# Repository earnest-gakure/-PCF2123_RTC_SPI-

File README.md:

# -PCF2123_RTC_SPI-
## Designed in KiCad
  The PCF2123 is a CMOS1 Real-Time Clock (RTC) and calendar optimized for low power applications. Data is transferred serially via a Serial Peripheral Interface (SPI-bus).

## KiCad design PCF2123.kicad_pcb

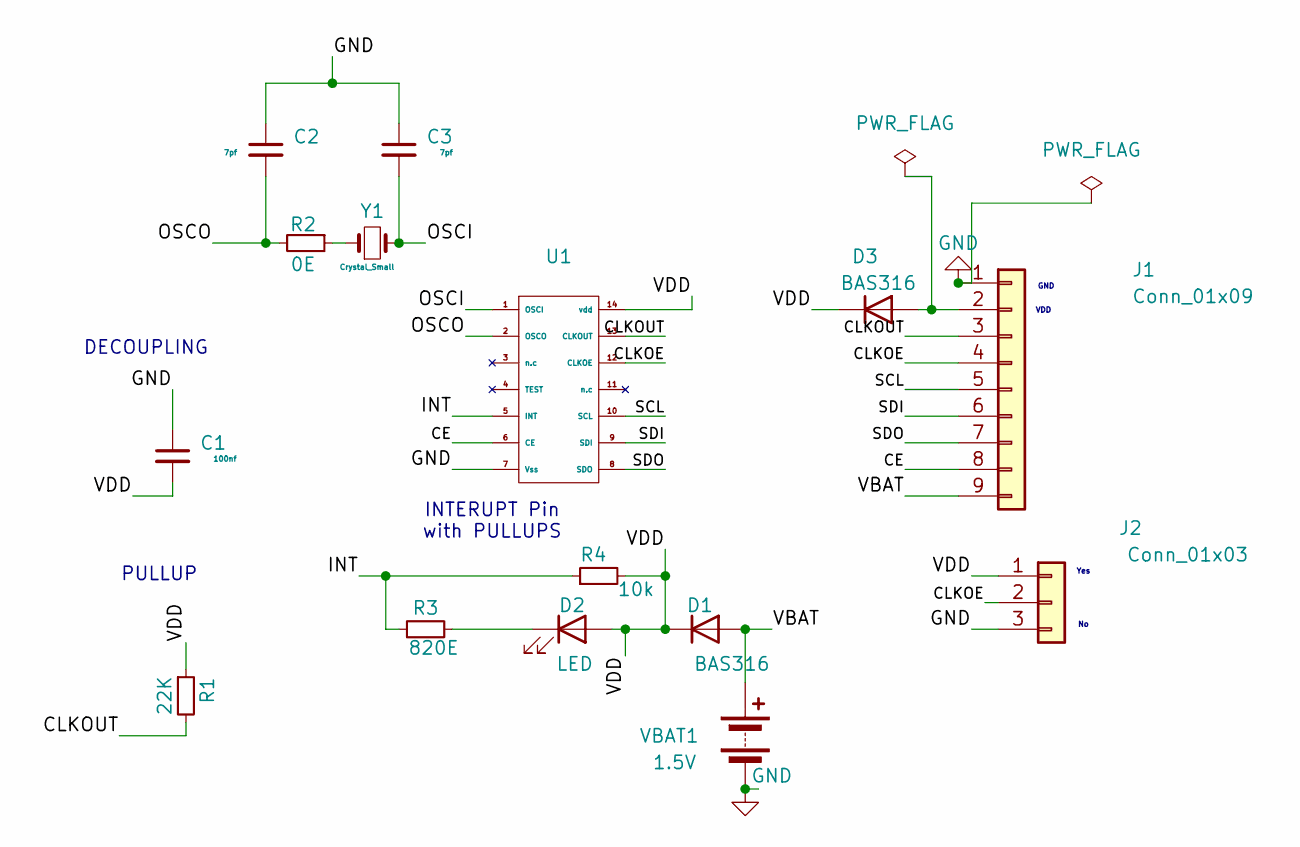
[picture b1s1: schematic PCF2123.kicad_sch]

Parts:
C1: 100nf; C_0805_2012Metric_Pad1.18x1.45mm_HandSolder
C2, C3: 7pf; C_0805_2012Metric_Pad1.18x1.45mm_HandSolder
D1, D3: BAS316; D_SMA-SMB_Universal_Handsoldering
D2: LED; LED_0805_2012Metric_Pad1.15x1.40mm_HandSolder
J1: Conn_01x09; PinHeader_1x09_P2.54mm_Vertical
J2: Conn_01x03; PinHeader_1x03_P2.54mm_Vertical
R1: 22K; R_1206_3216Metric_Pad1.30x1.75mm_HandSolder
R2: 0E; R_1206_3216Metric_Pad1.30x1.75mm_HandSolder
R3: 820E; R_1206_3216Metric_Pad1.30x1.75mm_HandSolder
R4: 10k; R_1206_3216Metric_Pad1.30x1.75mm_HandSolder
U1: PCF2123TS_RTC
VBAT1: 1.5V; BatteryHolder_ComfortableElectronic_CH273-2450_1x2450
Y1: Crystal_Small; Crystal_AT310_D3.0mm_L10.0mm_Horizontal

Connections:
/CE: J1.8, U1.6 (CE)
/CLKOE: J1.4, J2.2, U1.12 (CLKOE)
/CLKOUT: J1.3, R1.2, U1.13 (CLKOUT)
/INT: R3.1, R4.1, U1.5 (INT)
/OSCI: C3.2, U1.1 (OSCI), Y1.2
/OSCO: C2.2, R2.2, U1.2 (OSCO)
/SCL: J1.5, U1.10 (SCL)
/SDI: J1.6, U1.9 (SDI)
/SDO: J1.7, U1.8 (SDO)
/VBAT: D1.2 (A), J1.9, VBAT1.1 (+)
/VDD: C1.2, D1.1 (K), D2.2 (A), D3.1 (K), J2.1, R1.1, R4.2, U1.14 (vdd)
GND: C1.1, C2.1, C3.1, J1.1, J2.3, U1.7 (Vss), VBAT1.2 (-)
unnamed: D2.1 (K), R3.2
unnamed: D3.2 (A), J1.2
unnamed: R2.1, Y1.1

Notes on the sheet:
GND
PULLUP
INTERUPT Pin with PULLUPS
DECOUPLING
VDD
Yes

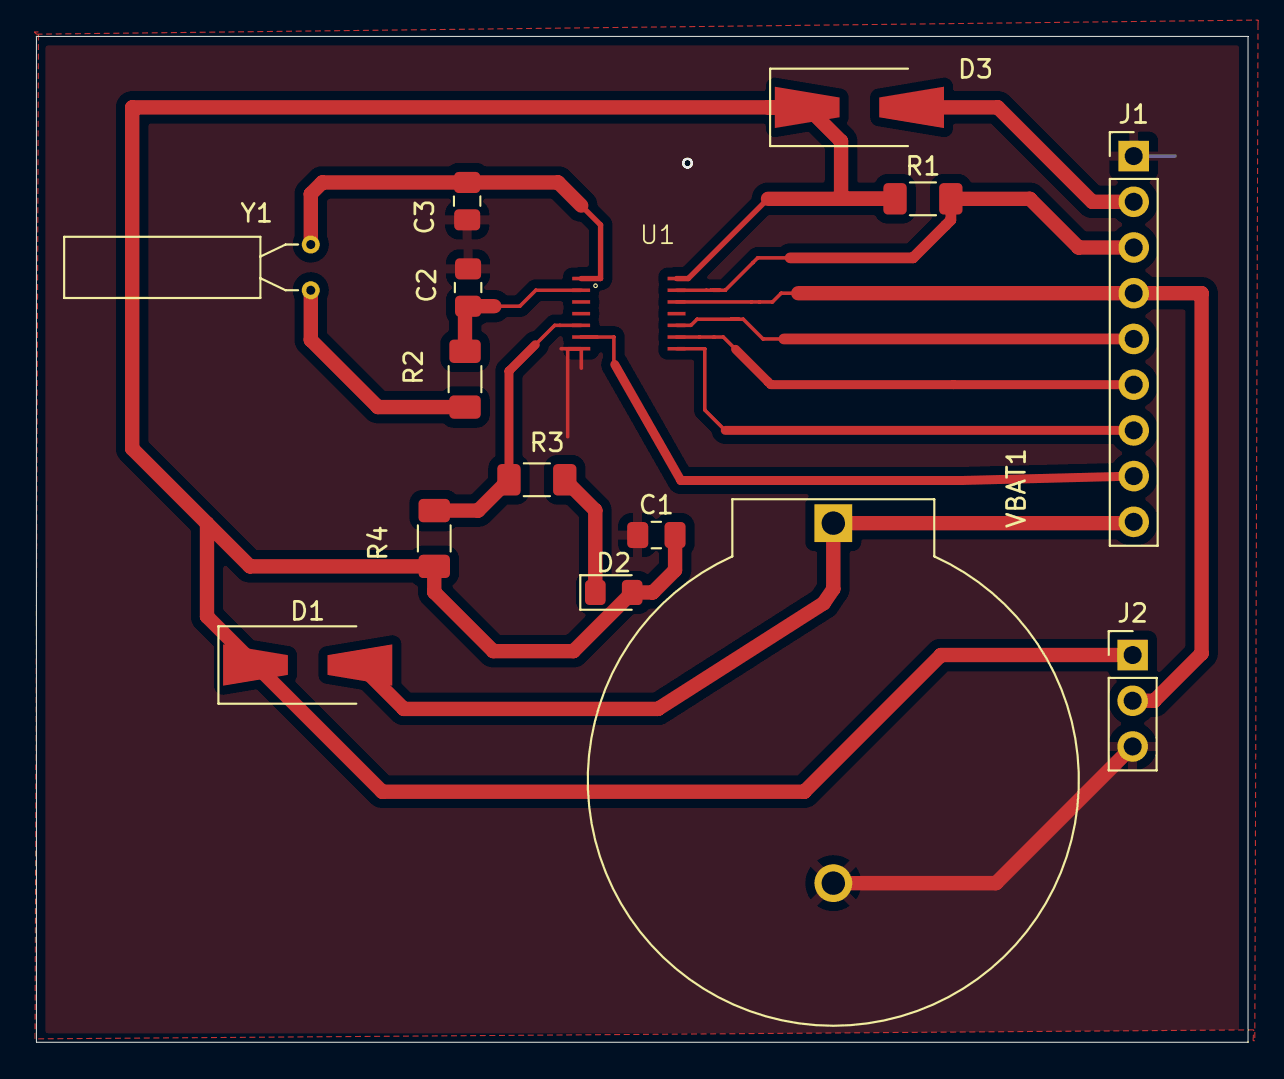
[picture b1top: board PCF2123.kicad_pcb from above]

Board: 2 copper layers, 67.3 x 55.9 mm, 15 parts (0 on the bottom side), 15 nets.
